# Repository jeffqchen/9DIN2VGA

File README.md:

# 9DIN2VGA

A dongle for consoles with 9 pin Mini DIN RGBs video output. This belong to my [series of VGA adapters](https://github.com/jeffqchen/Console-VGA-Dongle-Series) for various retro consoles and video equipments.

-----------

This adapter allows you to plug into consoles that output RGBS and stereo audio via a 9 pin Mini DIN jack and transmits the signals through a VGA cable. This includes but not limited to:
- Sega Genesis/Mega Drive 2
- Sega Genesis/Mega Drive 1 with the [Triple Bypass mod](https://github.com/tianfeng33/triple-bypass-Version-2)
- TerraOnion SSDS3
- [3DORGB](https://github.com/citrus3000psi/3DORGB) with 9 pin mini DIN option

The default sync signal used in this design is CSync. If you prefer composite video as sync, you can change it via the jumper by cutting the default connection and soldering the CVBS end in.

 Audio can be sent within the VGA cable, or extracted from the 3.5mm jack on the dongle. Buzzing may be noticeable when audio is transmitted through the VGA cable in certain scenes in certain games. This is due to insufficient shielding in most VGA cables. If you find the buzzing to be annoying, please use the 3.5mm jack on the dongle for audio output. This will ensure the cleanest possible audio.

-----------

## Parts

- PCB
  - [Main](https://oshpark.com/shared_projects/VMGQWaYo)
  - [Top Sub - **0.8mm thickness**](https://oshpark.com/shared_projects/PPJPpJ3M)
  - [Bottom Sub - **0.8mm thickness**](https://oshpark.com/shared_projects/QY4wR3iT)

  **Note the Top & Bottom sub boards MUST be ordered with the 0.8mm thickness option, otherwise they won't fit!**

- 9 pin Mini DIN Male Plug, Cable Type (Choose the 9PIN option) - [Link](https://github.com/jeffqchen/JeffParts/blob/main/Connectors/Mini%20DIN/9Pin/Cable/info.md)

- VGA Port Slim Female - [Link](https://github.com/jeffqchen/JeffParts/blob/main/Connectors/HD15/Slim/Female%20PCB/info.md)

- 3.5mm Headphone Jack - [Link](https://github.com/jeffqchen/JeffParts/blob/main/Connectors/3.5mm%20Audio%20Jack/Vertical%205-Pin%20PCB/info.md)

- [2x] M2x20mm and [1x] M2x6mm screw and hex nut - [Link](https://github.com/jeffqchen/JeffParts/blob/main/Parts/M2%20M3%20Hex%20Screw%20%26%20Nut/info.md)

Components:
- [4x] 220uF / 6.3V / Imperial 1206 Size - [[Link](https://github.com/jeffqchen/JeffParts/blob/main/Components/220uF%20SMD%20Cap/info.md)]
- [2x] SMD Capacitor 10uF 6.3V, 0603 size
- [1x] SMD Resistor 470 Ohm, 0603 size
- [3x] SMD Resistor 75 Ohm, 0603 size

-----------
## Print

Print the parts with the mating surface downwards, with support.

-----------
## Assembly

(Borrowing some pictures from the [8DIN2VGA Plug Type](https://github.com/jeffqchen/8DIN2VGA/tree/main/8DIN2VGA_Plug) guide)

### Disassemble The Plug First

Take apart the 9 pin mini DIN connector by removing the rubber outer casing, and then splitting the hard plastic inner casing to reveal the metal shielding. You may discard the rubber and plastic parts.

Then, use a pair of pliers to slightly open up the rear end of the metal barrel shielding, while pushing the plug core (black plastic with the pins) inward with another tool from the front, to remove the core from the metal shielding.

Do **NOT** spread the metal shielding by too much or you'll have to spend some time to bend it back into it's original shape afterwards.

You may also want to take this chance to slightly sand the left and right side of the outside of the metal shield, around the rear end, so it will be easier for solder to stick to the shielding later.

---------------

Soldering the plug PCBs in this project is essential and somewhat challenging. This applies to soldering the sub boards to the pin header, as well as the landing pads on the main PCB. If you leave any gap, the assembly will not fit and the shells won't close properly.

**DO NOT solder the plug PCBs to the main PCB at this stage.**

First, temporarily assemble the 3 boards together into their final position, and fix the assembly with the help from a pair of reverse tweezers or clamps. Fit the 0.8mm PCBs in between the gaps between the back side of the 3 rows of pins. Push the sub PCBs all the way until they touch the base of the pin. Make sure the pins and their pads are aligned properly.

 ----

**IMPORTANT**

 *The plastic of the plug core is weak against heat and should not be heated for more than a few seconds in one go. Try to cool it down between soldering by blowing air on it.*

 ----

 Solder the two pins on the bottom side of the **bottom** PCB with proper amount of solder. Then release the clamping and remove the top and main PCB. Proceed to solder the center row of the pins to the **bottom** PCB.

 Again, put everything back together with clamping. Then, solder the **top** PCB to the **top** row of the pin header. Now, release the clamping and remove only the main PCB. The assembly should look as follows:

 Shove the plug core - PCB assembly into the metal barrel shielding from the back, push it all the way in. Be careful and don't bend the PCB and damage the assembly.

 Fit the main PCB firmly into the shell and the plug and see if all the landing pads line up correctly:

------

On the main PCB, solder in all the SMD components, as well as the headphone jack. Do **NOT** solder in the VGA plug yet.

After soldering the headphone jack, use a side cutter to trim the protruding leads from it.

Tin the L-shape exposed area with a small amount of solder on both sides.

Note the default configuration of this adapter uses the CSync signal for sync. If you wish to use composite video for sync, you need to cut the connection between the triangle end and the center pad of the jumper, and then solder the CVBS pad with the center pad. You can also omit one of the 220uF capacitor for the sync line and the 470 Ohm resistor in this configuration, since they serve to decouple and attenuate the CSync signal.

------

### Plug Insertion

Insert the plug assembly into the inner side of the 3D printed shell. Align the hole on the shielding with the hole on the top side of the inner shell.

Trim the thread end of a M2x6mm machined screw so that its total length is 5.5mm (no more than 6mm). You may want to re-tap the end of the trimmed screw with a nut before moving onto the next step, since it's will make the next step a bit smoother.

Use a pair of tweezers, hold the nut and slide it inside the shielding cavity without letting go. Align the hole of the nut with the hole on the shell. With the other hand, put the screw in with a screw driver and screw into the nut. Screw all the way in until the screw is snug.

Check and make sure the end of the screw is **NOT** touching the plug PCB.

-----

### Main PCB Soldering

Again, insert the main PCB into its final position. Pinch the two sub boards into the main with a clamp or reverse tweezers. Make sure there's no gap between the sub and main PCB. Then, solder all the landing pads with proper amount of solder.

Then, use ample amount of solder to attach the metal shield of the plug to the exposed copper area onto both sides of the main PCB. There are a total of four points to solder to the shielding. Make sure you don't apply too much heat for too long, or you might warp the 3D printed case.

Last, solder in the VGA port and trim the shielding prongs with a side cutter.

Soldering is finished.

------

### The End

Take a M2 screw, screw a nut onto it, and use the screw as a handle to push the nut into the nut slot on inner shell.

Then, slide the outer shell into position with inner shell and put in two M2x20mm screws to close up the shell.

------
## Special Thanks

Tianfeng (for verifying some uncertainties)
- [Twitter](https://twitter.com/Tian_Feng44)

-----
Shield: [![CC BY-SA 4.0][cc-by-sa-shield]][cc-by-sa]

This work is licensed under a
[Creative Commons Attribution-ShareAlike 4.0 International License][cc-by-sa].

[![CC BY-SA 4.0][cc-by-sa-image]][cc-by-sa]

[cc-by-sa]: http://creativecommons.org/licenses/by-sa/4.0/
[cc-by-sa-image]: https://licensebuttons.net/l/by-sa/4.0/88x31.png
[cc-by-sa-shield]: https://img.shields.io/badge/License-CC%20BY--SA%204.0-lightgrey.svg

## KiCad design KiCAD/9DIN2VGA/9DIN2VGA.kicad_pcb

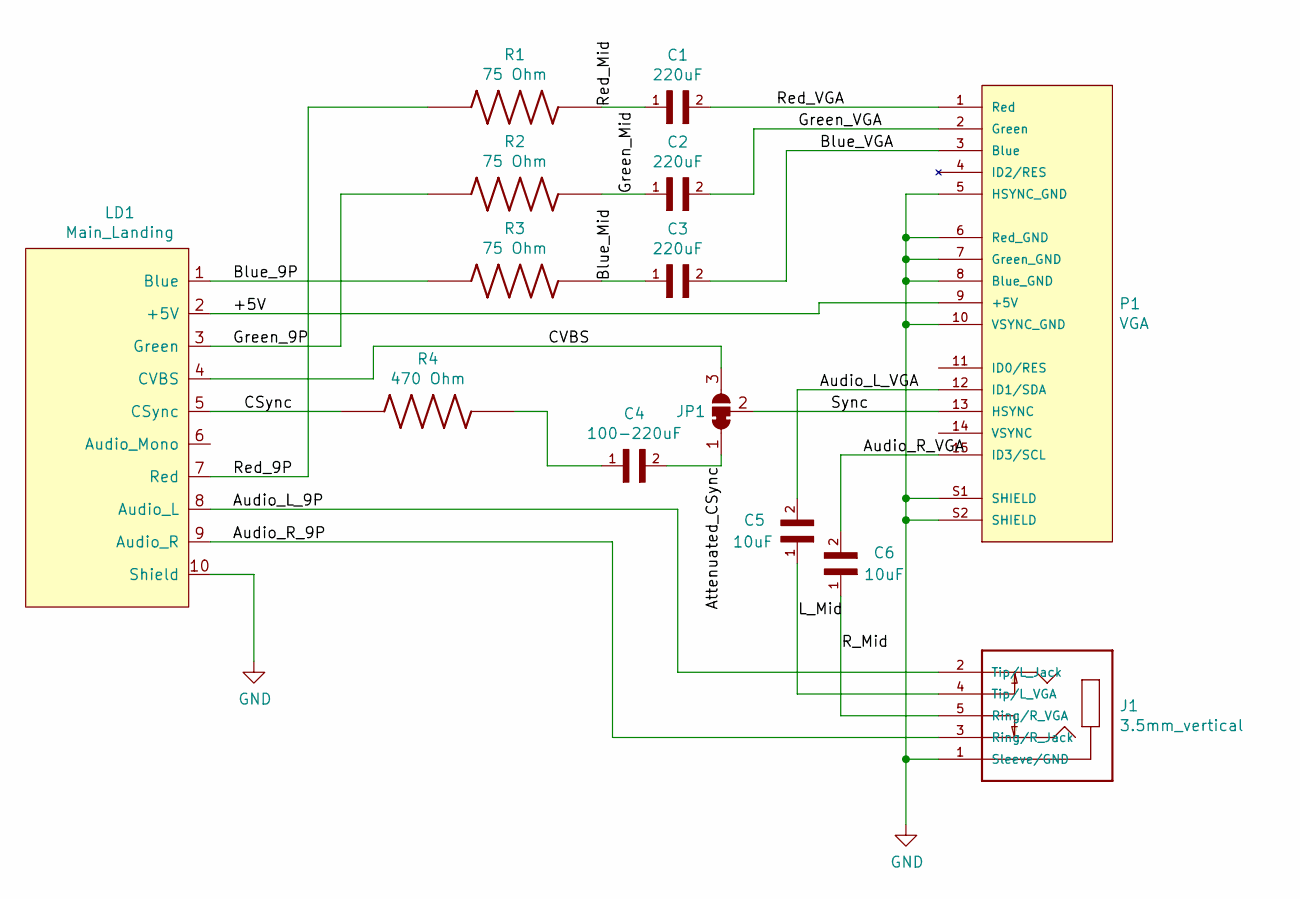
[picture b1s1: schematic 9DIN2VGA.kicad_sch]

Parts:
C1, C2, C3: 220uF; C_1206_3216Metric
C4: 100-220uF; C_1206_3216Metric
C5, C6: 10uF; C_0603_1608Metric
J1: 3.5mm_vertical; PARTREV 1.01
JP1: SolderJumper_3_Bridged12; SolderJumper-3_P1.3mm_Bridged12_RoundedPad1.0x1.5mm
LD1: Main_Landing; Main_PCB_Landing_Pads
P1: VGA; VGA_female_rightangle_slim; PARTREV N/A
R1, R2, R3: 75 Ohm; R_0603_1608Metric
R4: 470 Ohm; R_0603_1608Metric

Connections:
/+5V: LD1.2 (+5V), P1.9 (+5V)
/Attenuated_CSync: C4.2, JP1.1 (A)
/Audio_L_9P: J1.2 (Tip/L_Jack), LD1.8 (Audio_L)
/Audio_L_VGA: C5.2, P1.12 (ID1/SDA)
/Audio_R_9P: J1.3 (Ring/R_Jack), LD1.9 (Audio_R)
/Audio_R_VGA: C6.2, P1.15 (ID3/SCL)
/Blue_9P: LD1.1 (Blue), R3.1
/Blue_Mid: C3.1, R3.2
/Blue_VGA: C3.2, P1.3 (Blue)
/CSync: LD1.5 (CSync), R4.1
/CVBS: JP1.3 (B), LD1.4 (CVBS)
/Green_9P: LD1.3 (Green), R2.1
/Green_Mid: C2.1, R2.2
/Green_VGA: C2.2, P1.2 (Green)
/L_Mid: C5.1, J1.4 (Tip/L_VGA)
/R_Mid: C6.1, J1.5 (Ring/R_VGA)
/Red_9P: LD1.7 (Red), R1.1
/Red_Mid: C1.1, R1.2
/Red_VGA: C1.2, P1.1 (Red)
/Sync: JP1.2 (C), P1.13 (HSYNC)
GND: J1.1 (Sleeve/GND), LD1.10 (Shield), P1.5 (HSYNC_GND), P1.6 (Red_GND), P1.7 (Green_GND), P1.8 (Blue_GND), P1.10 (VSYNC_GND), P1.S1 (SHIELD), P1.S2 (SHIELD)
unnamed: C4.1, R4.2

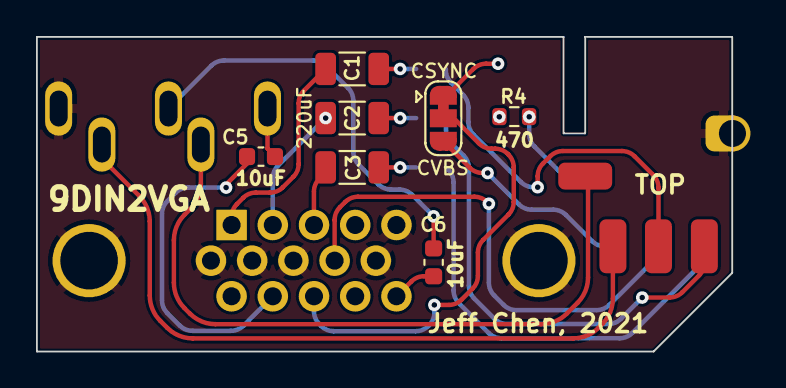
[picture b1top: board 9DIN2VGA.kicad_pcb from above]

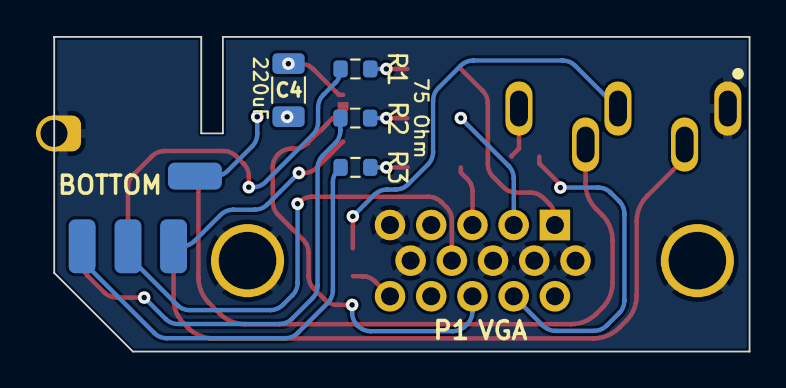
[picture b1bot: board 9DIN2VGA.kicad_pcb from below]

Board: 2 copper layers, 38.6 x 17.5 mm, 14 parts (6 on the bottom side), 22 nets.

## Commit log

2021-12-28 Initial upload
2021-12-29 3D printed shell
2021-12-29 Why this file
2022-08-09 Change license type
2026-03-15 Update quantity of SMD Resistor 75 Ohm in README
